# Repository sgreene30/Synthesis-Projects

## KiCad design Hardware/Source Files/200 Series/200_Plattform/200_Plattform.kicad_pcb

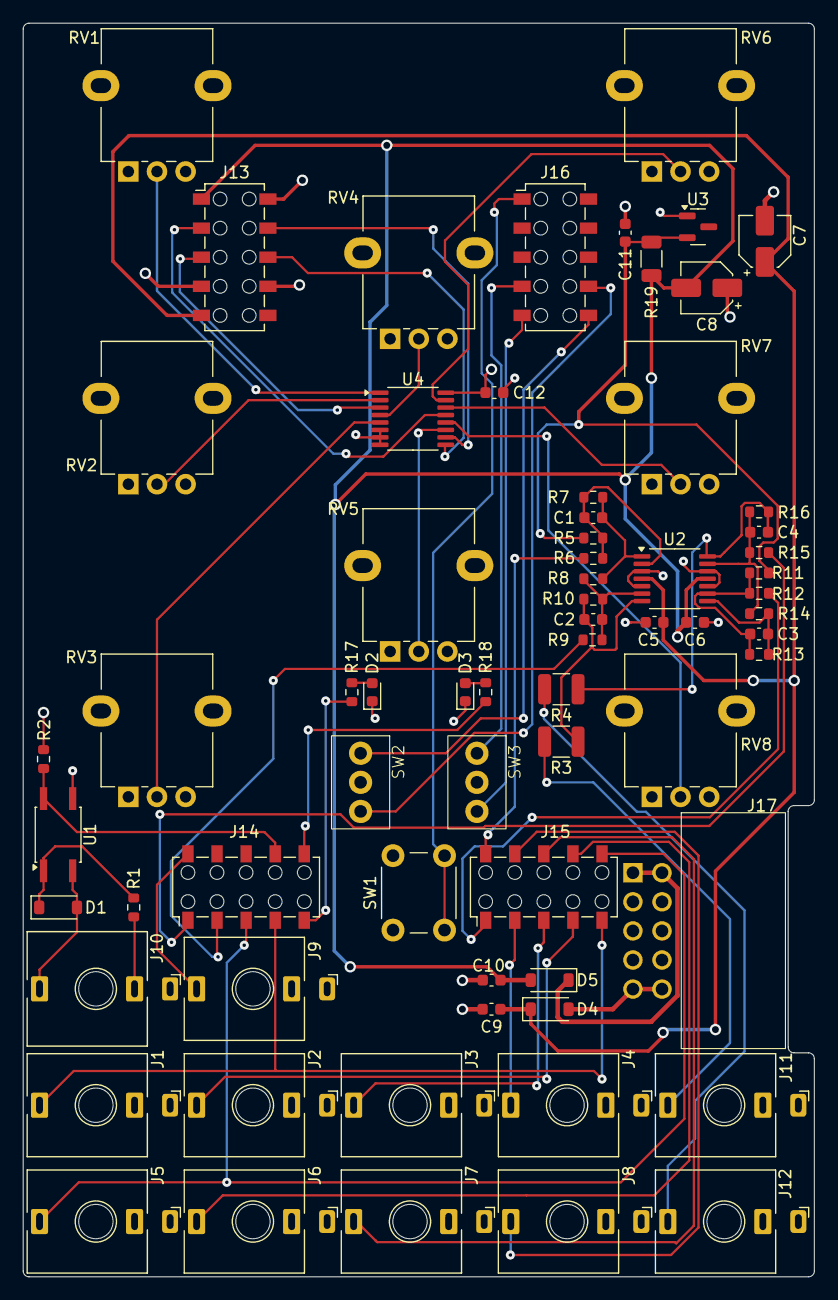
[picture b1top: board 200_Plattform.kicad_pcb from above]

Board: 4 copper layers, 69.1 x 109.5 mm, 69 parts (1 on the bottom side), 55 nets.

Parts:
C1, C2, C3, C4: 180pF; C_0603_1608Metric
C5, C6, C9, C10, C11, C12: 100nF; C_0603_1608Metric
C7, C8: 10uF; CAP_EEE-FK1V100UR
D1, D4, D5: MBR0530; D_SOD-123
D2, D3: LED_BLUE; LED_0603_1608Metric
J1, J2, J3, J4, J5, J6, J7, J8, J9, J11, J12: THONKICONN_MONO; JACK_THONKICONN_MONO_WQP518MA
J10: THONKICONN STEREO; JACK_THONKICONN_STEREO_WQP419GR
J13, J14, J15, J16: HEADER_2X10_BOTTOM_ENTRY_966210-2000-AR-PR
J17: EURO_POWER_10_RTANG
M1: DAISY PATCH SM; DAISY_PATCH_SM_OUTLINE
R1, R2, R17, R18: 220R; R_0603_1608Metric
R3, R4: 1k 0.5W; R_1210_3225Metric
R5, R7, R11, R13: 20k; R_0603_1608Metric
R6, R8, R9, R10, R12, R14, R15, R16: 10k; R_0603_1608Metric
R19: 6.8k 0.25W; R_1206_3216Metric
RV1, RV2, RV3, RV4, RV5, RV6, RV7, RV8: 10k; ALPHAPOT
SW1: SW_TACTILE; SW_TACTILE_TL1105SPF250Q
SW2, SW3: SW_SPDT_ON_OFF_ON_SUBMINI; SW_TOGGLE_2MS3T1B3M2QES
U1: LTV-355T; SO-4_4.4x3.6mm_P2.54mm
U2: TL074CPWR; TSSOP-14_4.4x5mm_P0.65mm
U3: LM4040CIM3-5.0; SOT-23
U4: CD4052B; TSSOP-16_4.4x5mm_P0.65mm

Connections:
+3.3V: C12.1, J13.10 (X10), R2.2, RV1.3, RV2.3, RV3.3, RV4.3, RV5.3, RV6.3, RV7.3, RV8.3, U4.16 (VDD)
+12V: C5.1, C7.1, C9.1, D4.1 (K), J13.5 (X5), U2.4 (V+)
-5V: C11.1, R5.1, R11.1, R19.1, U3.2 (A)
-12V: C6.2, C8.2, C10.2, D5.2 (A), J13.1 (X1), R19.2, U2.11 (V-)
/Jacks/MIDI_SINK: D1.2 (A), J10.T, U1.2
/Jacks/MIDI_SOURCE: J10.R, R1.1
AUDIO_LEFT: J14.2 (X2), R9.1
AUDIO_RIGHT: J14.1 (X1), R15.1
CV_OUT_1: J15.10 (X10), R6.2
CV_OUT_2: J15.1 (X1), R12.2
GATE_IN: J9.T, J14.10 (X10)
GND: C5.2, C6.1, C7.2, C8.1, C9.2, C10.1, C11.2, C12.2, D2.1 (K), D3.1 (K), J1.S, J2.S, J3.S, J4.S, J5.S, J6.S, J7.S, J8.S, J9.S, J11.S, J12.S, J13.4 (X4), J13.7 (X7), J17.3 (gnd), J17.4 (gnd), J17.5 (gnd), J17.6 (gnd), J17.7 (gnd), J17.8 (gnd), RV1.1, RV2.1, RV3.1, RV4.1, RV5.1, RV6.1, RV7.1, RV8.1, SW1.1, SW1.2, SW2.2 (B), SW3.2 (B), U1.3, U2.3 (+), U2.5 (+), U2.10 (+), U2.12 (+), U3.1 (K), U4.6 (INH), U4.7 (VEE), U4.8 (VSS)
LED_LEFT: J14.5 (X5), R17.2
LED_RIGHT: J14.6 (X6), R18.2
MIDI_UART_RX: J14.7 (X7), R2.1, U1.4
unnamed: C1.2, R7.2, R8.1, U2.1
unnamed: C3.2, R13.2, R14.1, U2.8
unnamed: D1.1 (K), R1.2, U1.1
unnamed: D2.2 (A), R17.1
unnamed: D3.2 (A), R18.1
unnamed: D4.2 (A), J17.9 (+12V), J17.10 (+12V)
unnamed: D5.1 (K), J17.1 (-12V), J17.2 (-12V)
unnamed: J11.T, R3.2
unnamed: J12.T, R4.2
unnamed: C1.1, R5.2, R6.1, R7.1, U2.2 (-)
unnamed: C2.1, R8.2, R9.2, R10.1, U2.6 (-)
unnamed: C3.1, R11.2, R12.1, R13.1, U2.9 (-)
unnamed: C4.1, R14.2, R15.2, R16.1, U2.13 (-)
POT_MUX_A: J13.9 (X9), U4.10 (A)
POT_MUX_ADC_X: J13.2 (X2), U4.13 (X)
POT_MUX_ADC_Y: J13.3 (X3), U4.3 (Y)
POT_MUX_B: J13.8 (X8), U4.9 (B)
TACTILE_SW: J16.1 (X1), SW1.3 (K), SW1.4 (A)
TOGGLE1_1: J16.6 (X6), SW2.1 (A)
TOGGLE1_3: J16.7 (X7), SW2.3 (C)
TOGGLE2_1: J16.4 (X4), SW3.1 (A)
TOGGLE2_3: J16.5 (X5), SW3.3 (C)
analog_out_1: C2.2, R3.1, R10.2, U2.7
analog_out_2: C4.2, R4.1, R16.2, U2.14
in_1: J1.T, J14.4 (X4), J15.5 (X5)
in_2: J2.T, J15.4 (X4)
in_3: J3.T, J15.3 (X3)
in_4: J4.T, J15.2 (X2)
in_5: J5.T, J14.3 (X3), J15.6 (X6)
in_6: J6.T, J15.7 (X7)
in_7: J7.T, J15.8 (X8)
in_8: J8.T, J15.9 (X9)
pot_1: RV1.2, U4.1 (Y0)
pot_2: RV2.2, U4.2 (Y2)
pot_3: RV3.2, U4.5 (Y1)
pot_4: RV4.2, U4.4 (Y3)
pot_5: RV5.2, U4.11 (X3)
pot_6: RV6.2, U4.15 (X2)
pot_7: RV7.2, U4.14 (X1)
pot_8: RV8.2, U4.12 (X0)

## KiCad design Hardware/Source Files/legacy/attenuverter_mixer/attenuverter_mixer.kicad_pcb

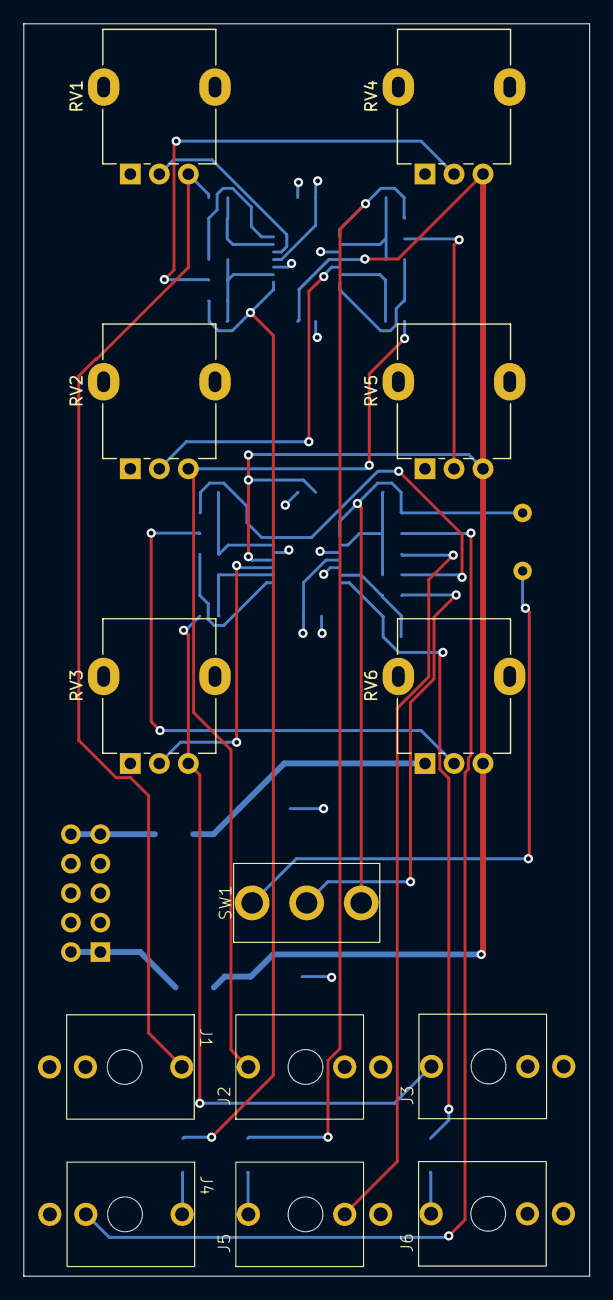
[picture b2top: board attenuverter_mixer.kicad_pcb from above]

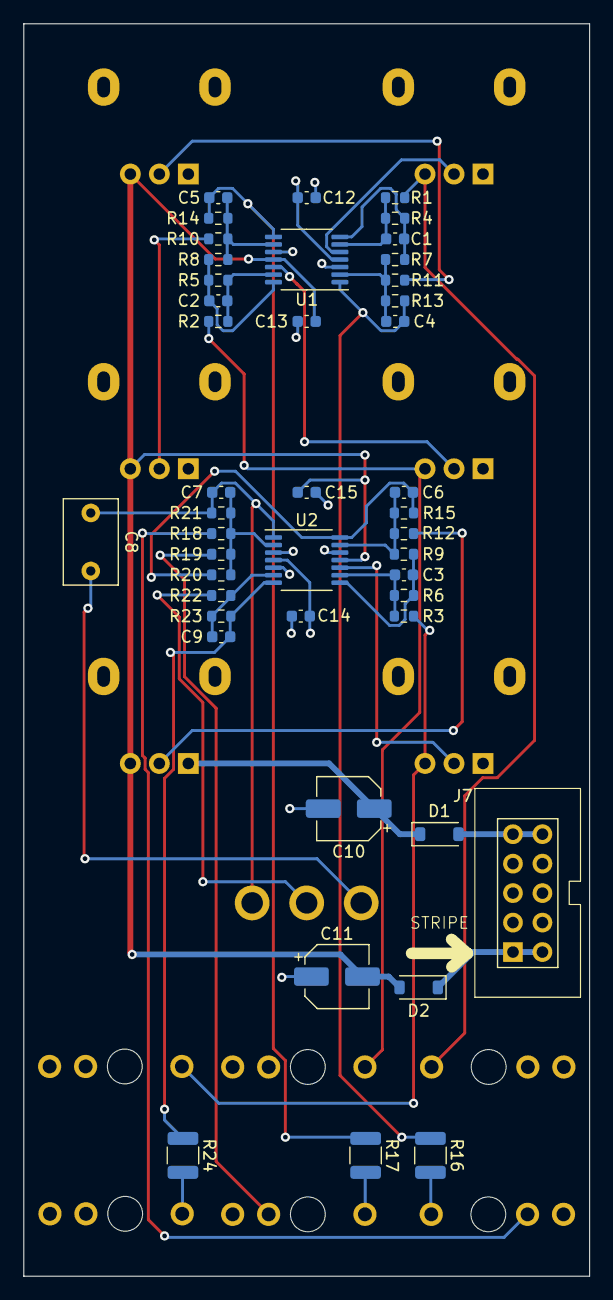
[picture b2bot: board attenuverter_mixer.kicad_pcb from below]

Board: 4 copper layers, 48.8 x 107.9 mm, 57 parts (44 on the bottom side), 37 nets.

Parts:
C1, C2, C3, C4, C5, C6, C7, C9: 47pF; C_0603_1608Metric
C8: 2.2uF; C_Rect_L7.2mm_W4.5mm_P5.00mm_FKS2_FKP2_MKS2_MKP2
C10, C11: 10uF; CP_Elec_5x5.3
C12, C13, C14, C15: 100nF; C_0603_1608Metric
D1, D2: MBR0530; D_SOD-123
J1, J2, J3, J4, J5, J6: thonkiconn
J7: euro_power_10; eurorack_10
R1, R2, R3, R4, R5, R6, R18, R19, R20, R23: 100k; R_0603_1608Metric
R7, R8, R9, R13, R14, R15: 10k; R_0603_1608Metric
R10, R11, R12, R21, R22: 24k; R_0603_1608Metric
R16, R17, R24: 1k 0.5W; R_1210_3225Metric
RV1, RV2, RV3, RV4, RV5, RV6: 10k; Potentiometer_Alpha_RD901F-40-00D_Single_Vertical
SW1: SW_ON_ON_SPDT_MINI; Mini_sw
U1, U2: TL074; TSSOP-14_4.4x5mm_P0.65mm

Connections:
+12V: C10.1, C12.1, C14.1, D1.1 (K), RV4.1, RV5.1, RV6.1, U1.4 (V+), U2.4 (V+)
-12V: C11.2, C13.2, C15.2, D2.2 (A), RV4.3, RV5.3, RV6.3, U1.11 (V-), U2.11 (V-)
/Power/V+_IN: D1.2 (A), J7.9 (+12V), J7.10 (+12V)
/Power/V-_IN: D2.1 (K), J7.1 (-12V), J7.2 (-12V)
GND: C10.2, C11.1, C12.2, C13.1, C14.2, C15.1, J1.S, J2.S, J3.S, J4.S, J5.S, J6.S, J7.3 (gnd), J7.4 (gnd), J7.5 (gnd), J7.6 (gnd), J7.7 (gnd), J7.8 (gnd), RV1.1, RV2.1, RV3.1, U1.3 (+), U1.10 (+), U2.3 (+), U2.5 (+), U2.12 (+)
unnamed: C1.2, R4.2, R7.1, U1.7
unnamed: C2.2, R5.2, R8.1, U1.14
unnamed: C3.2, R6.2, R9.1, U2.8
unnamed: C4.2, R13.2, R16.1, U1.1
unnamed: C5.2, R14.2, R17.1, U1.8
unnamed: C9.2, R23.2, R24.1, U2.7
unnamed: J1.T, R1.1, RV1.3
unnamed: J2.T, R2.1, RV2.3
unnamed: J3.T, R3.1, RV3.3
unnamed: J4.T, R16.2
unnamed: J5.T, R17.2
unnamed: J6.T, R24.2
unnamed: C7.2, C8.1, R21.2, SW1.1 (A), U2.1
unnamed: R22.1, SW1.2 (B)
unnamed: C8.2, SW1.3 (C)
unnamed: C4.1, R7.2, R11.2, R13.1, U1.2 (-)
unnamed: RV1.2, U1.5 (+)
unnamed: C1.1, R1.2, R4.1, U1.6 (-)
unnamed: C5.1, R8.2, R10.2, R14.1, U1.9 (-)
unnamed: RV2.2, U1.12 (+)
unnamed: C2.1, R2.2, R5.1, U1.13 (-)
unnamed: C7.1, R18.2, R19.2, R20.2, R21.1, U2.2 (-)
unnamed: C9.1, R22.2, R23.1, U2.6 (-)
unnamed: RV3.2, U2.10 (+)
unnamed: C3.1, R3.2, R6.1, U2.9 (-)
unnamed: C6.1, R9.2, R12.2, R15.1, U2.13 (-)
att_1_out: J4.TN, R18.1
att_2_out: J5.TN, R19.1
att_3_out: C6.2, R15.2, R20.1, U2.14
offset_1: R11.1, RV4.2
offset_2: R10.1, RV5.2
offset_3: R12.1, RV6.2

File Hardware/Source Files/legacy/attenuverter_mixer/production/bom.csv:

Designator,Footprint,Quantity,Value,LCSC Part #
"C1, C2, C3, C4, C5, C6, C7, C9",0603,8,47pF,C105622
"C10, C11",CP_Elec_5x5.3,2,10uF,C7200666
"C12, C13, C14, C15",0603,4,100nF,C14663
C8,C_Rect_L7.2mm_W4.5mm_P5.00mm_FKS2_FKP2_MKS2_MKP2,1,2.2uF,C3780718
"D1, D2",D_SOD-123,2,MBR0530,C82046
J6,thonkiconn,1,thonkiconn,WQP518MA
"R1, R18, R19, R2, R20, R23, R3, R4, R5, R6",0603,10,100k,C14675
"R10, R11, R12, R21, R22",0603,5,24k, C137760
"R13, R14, R15, R7, R8, R9",0603,6,10k,C98220
"R16, R17, R24",1210,3,1k 0.5W,C83144
"U1, U2",TSSOP-14_4.4x5mm_P0.65mm,2,TL074,C96507
